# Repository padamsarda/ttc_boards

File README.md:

# Arduino TTC Shield

## Overview
This Arduino shield was made for testing and learning TTC systems. It combines both the nRF24L01 and LoRa RA-02 modules on a single board, making it easy to switch between short- and long-range wireless communication during development.

The board also includes an INA219 for power tracking, understanding the relation between Link-Budget and Power-Budget.

## Features
- Arduino Uno shield form factor
- nRF24L01 wireless module interface
- LoRa RA-02 module interface
- INA219 current sensing
- Jumper-selectable power for nRF24L01
- Jumper-selectable power for LoRa
- Boost converter for battery operation
- Battery connector
- Power indicator LED

## Applications
- TTC (Telemetry, Tracking and Command) development
- learning LoRa RA-02 and NRF24L01 
- Power consumption measurement of RF modules
- Rapid prototyping with Arduino

## Notes
This was my first actual pcb, made a few mistakes too
Designed and developed as part of **Team Anant**.

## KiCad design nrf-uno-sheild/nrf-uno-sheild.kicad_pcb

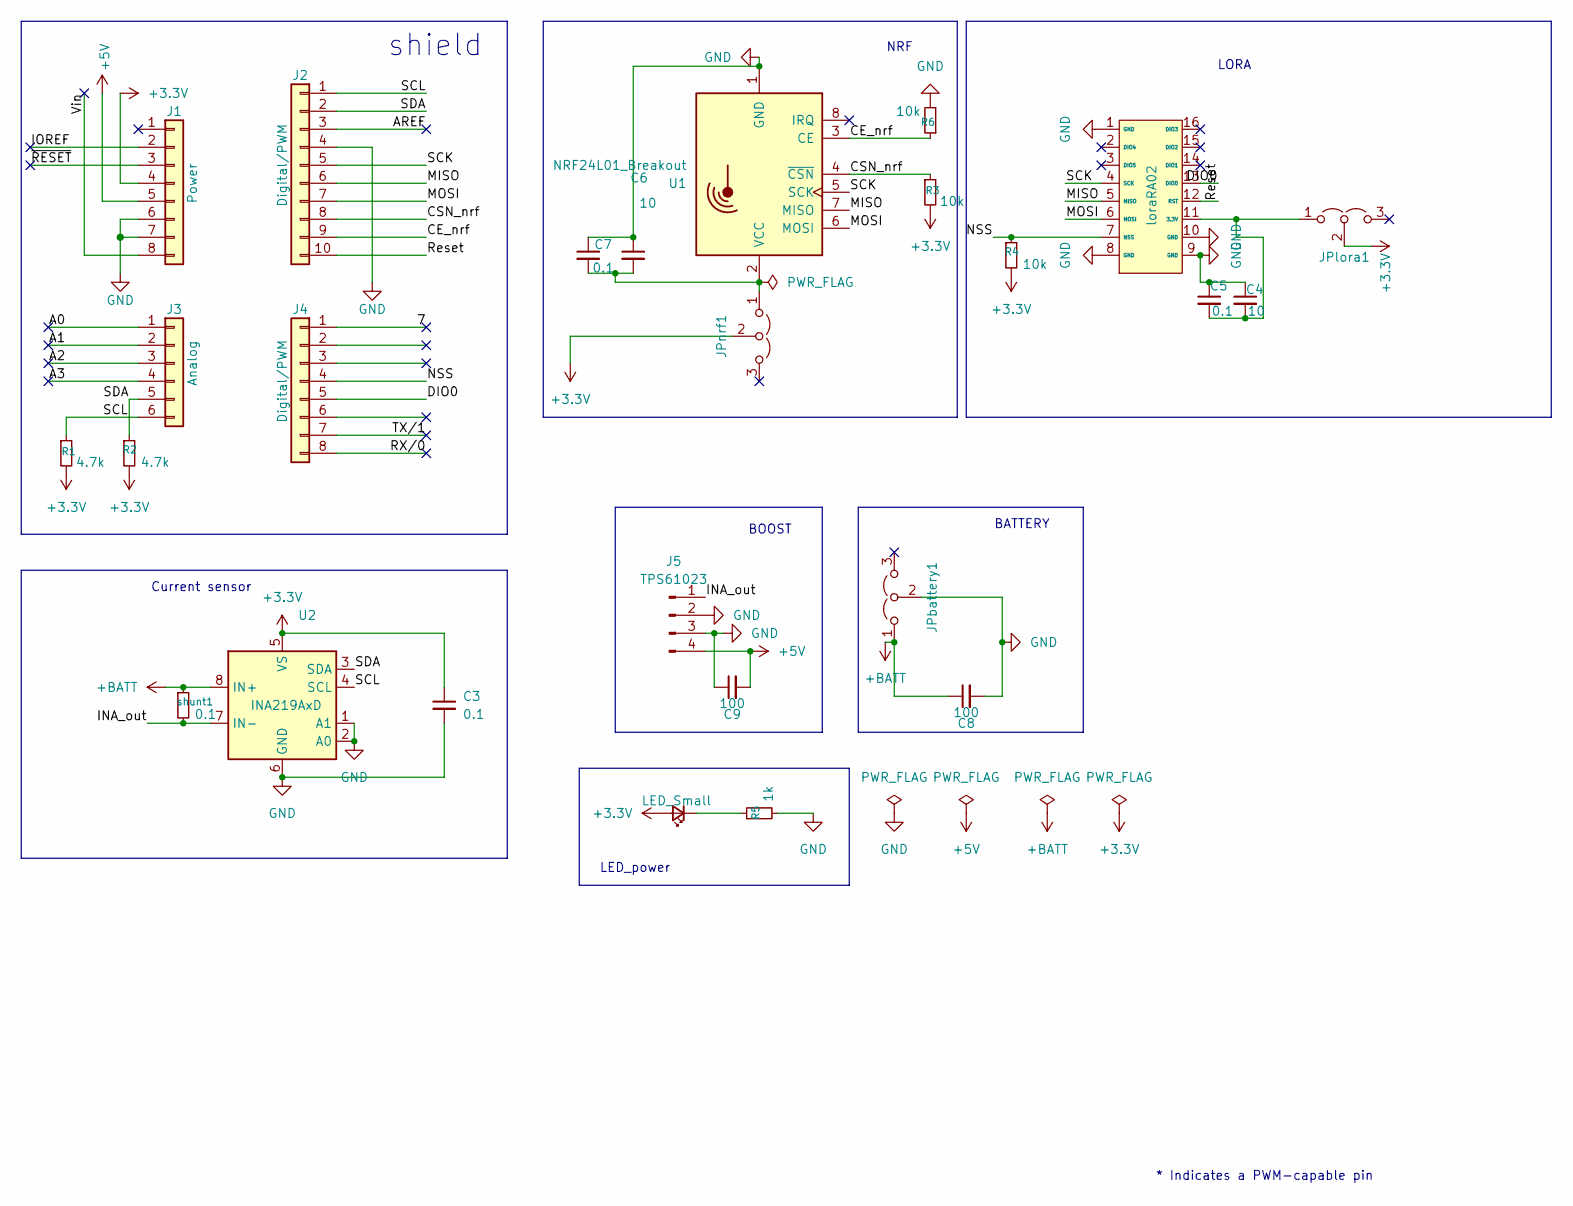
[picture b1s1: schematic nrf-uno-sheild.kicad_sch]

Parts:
C3, C5, C7: 0.1; C_0805_2012Metric
C4, C6: 10; C_0805_2012Metric
C8, C9: 100; C_0805_2012Metric
D1: LED_Small; LED_D3.0mm
J1: Power; PinSocket_1x08_P2.54mm_Vertical
J2: Digital/PWM; PinSocket_1x10_P2.54mm_Vertical
J3: Analog; PinSocket_1x06_P2.54mm_Vertical
J4: Digital/PWM; PinSocket_1x08_P2.54mm_Vertical
J5: TPS61023; PinHeader_1x04_P2.54mm_Vertical
JPbattery1: Jumper_3_Open; PinHeader_1x03_P2.54mm_Vertical
JPlora1: Jumper_3_Open; PinHeader_1x03_P2.54mm_Vertical
JPnrf1: Jumper_3_Open; PinHeader_1x03_P2.54mm_Vertical
R1, R2: 4.7k; R_0805_2012Metric
R3, R4, R6: 10k; R_0805_2012Metric
R5: 1k; R_0805_2012Metric
U1: NRF24L01_Breakout; nRF24L01_Breakout
U2: INA219AxD; SOIC-8_3.9x4.9mm_P1.27mm
loraRA02: loraRA02 breakout
shunt1: 0.1; R_2512_6332Metric

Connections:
+3.3V: C3.1, D1.2 (A), J1.4, JPlora1.2 (C), JPnrf1.2 (C), R1.2, R2.2, R3.2, R4.2, U2.5 (VS); also elsewhere on the board
+5V: C9.2, J1.5, J5.4
+BATT: C8.1, JPbattery1.1 (A), U2.8 (IN+), shunt1.1
/7: J4.1
/A0: J3.1
/A1: J3.2
/A2: J3.3
/A3: J3.4
/AREF: J2.3
/CE_nrf: J2.9, R6.1, U1.3 (CE); also elsewhere on the board
/CSN_nrf: J2.8, R3.1, U1.4 (~CSN); also elsewhere on the board
/DIO0: J4.5, loraRA02.13 (DIO0)
/INA_out: J5.1, U2.7 (IN-), shunt1.2
/IOREF: J1.2
/MISO: J2.6, U1.7 (MISO), loraRA02.5 (MISO); also elsewhere on the board
/MOSI: J2.7, U1.6 (MOSI), loraRA02.6 (MOSI); also elsewhere on the board
/NSS: J4.4, R4.1, loraRA02.7 (NSS)
/RX/0: J4.8
/Reset: J2.10, loraRA02.12 (RST)
/SCK: J2.5, U1.5 (SCK), loraRA02.4 (SCK); also elsewhere on the board
/SCL: J2.1, J3.6, R1.1, U2.4 (SCL)
/SDA: J2.2, J3.5, R2.1, U2.3 (SDA)
/TX/1: J4.7
/Vin: J1.8
/~RESET: J1.3
GND: C3.2, C4.1, C5.1, C6.1, C7.1, C8.2, C9.1, J1.6, J1.7, J2.4, J5.2, J5.3, JPbattery1.2 (C), R5.2, R6.2, U1.1 (GND), U2.1 (A1), U2.2 (A0), U2.6 (GND), loraRA02.1 (GND), loraRA02.8 (GND), loraRA02.9 (GND), loraRA02.10 (GND); also elsewhere on the board
unnamed: D1.1 (K), R5.1
unnamed: C4.2, C5.2, JPlora1.1 (A), loraRA02.11 (3.3V)
unnamed 28: C6.2, C7.2, JPnrf1.1 (A), U1.2 (VCC); also elsewhere on the board

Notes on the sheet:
Current sensor
BOOST
LORA
NRF
BATTERY
shield
LED_power
* Indicates a PWM-capable pin

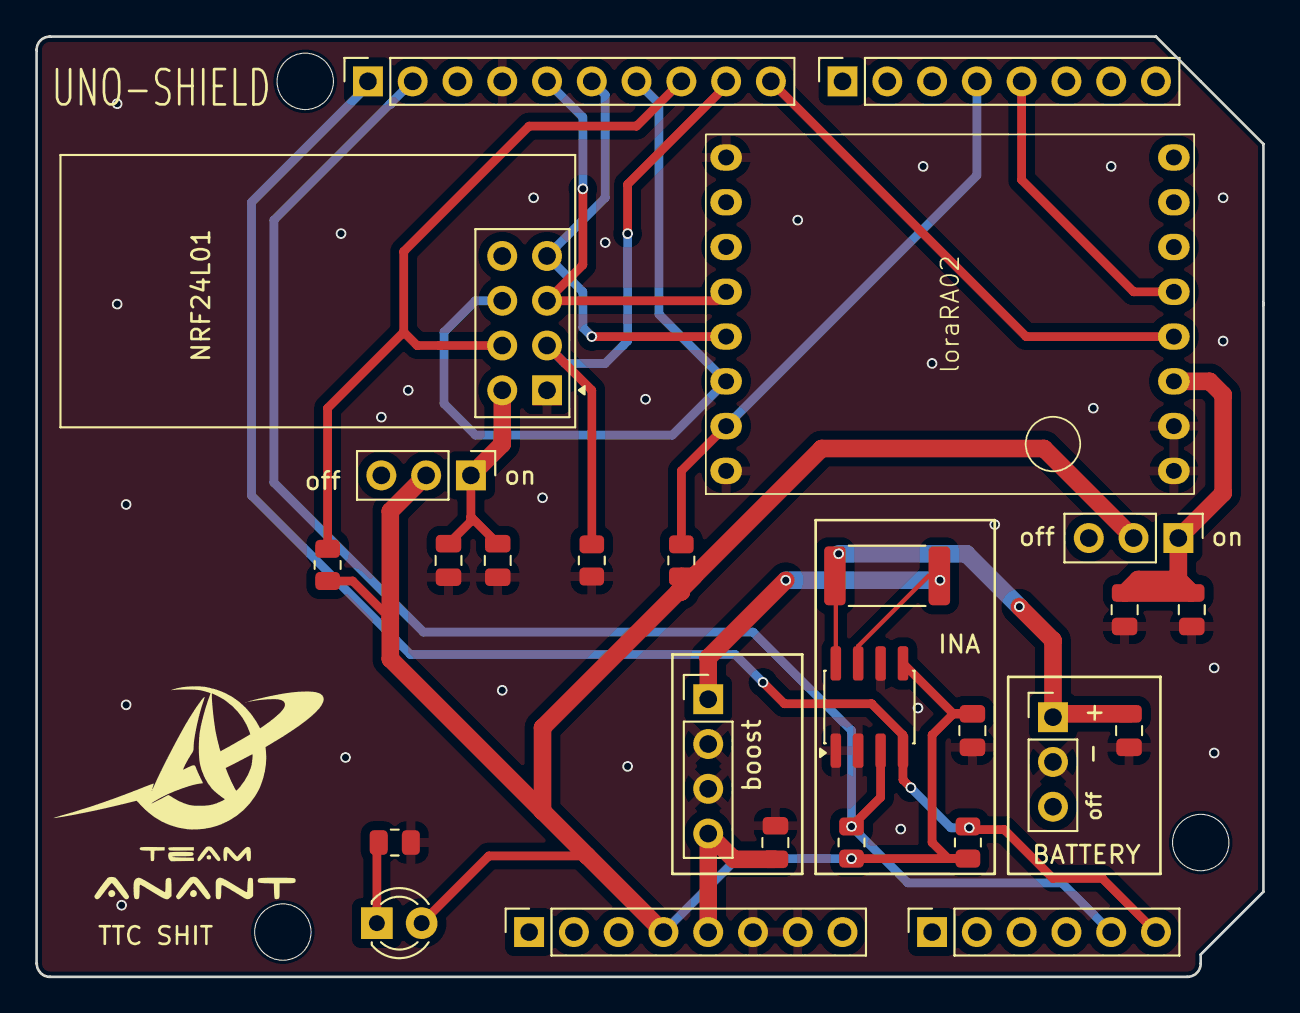
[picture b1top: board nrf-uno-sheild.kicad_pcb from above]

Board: 2 copper layers, 69.6 x 53.3 mm, 29 parts (0 on the bottom side), 18 nets.

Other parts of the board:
MH1, MH2, MH4: MountingHole_3.2mm
on: Jumper_3_Open; PinHeader_1x03_P2.54mm_Vertical
u1: NRF24L01_Breakout; nRF24L01_Breakout

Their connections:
+3.3V: on.2 (C); also elsewhere on the board
/CE_nrf: u1.3 (CE); also elsewhere on the board
/CSN_nrf: u1.4 (~CSN); also elsewhere on the board
/MISO: u1.7 (MISO); also elsewhere on the board
/MOSI: u1.6 (MOSI); also elsewhere on the board
/SCK: u1.5 (SCK); also elsewhere on the board
GND: u1.1 (GND); also elsewhere on the board
unnamed 28: on.1 (A), u1.2 (VCC); also elsewhere on the board

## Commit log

2026-04-20 uno_nrf_lora_board commit
